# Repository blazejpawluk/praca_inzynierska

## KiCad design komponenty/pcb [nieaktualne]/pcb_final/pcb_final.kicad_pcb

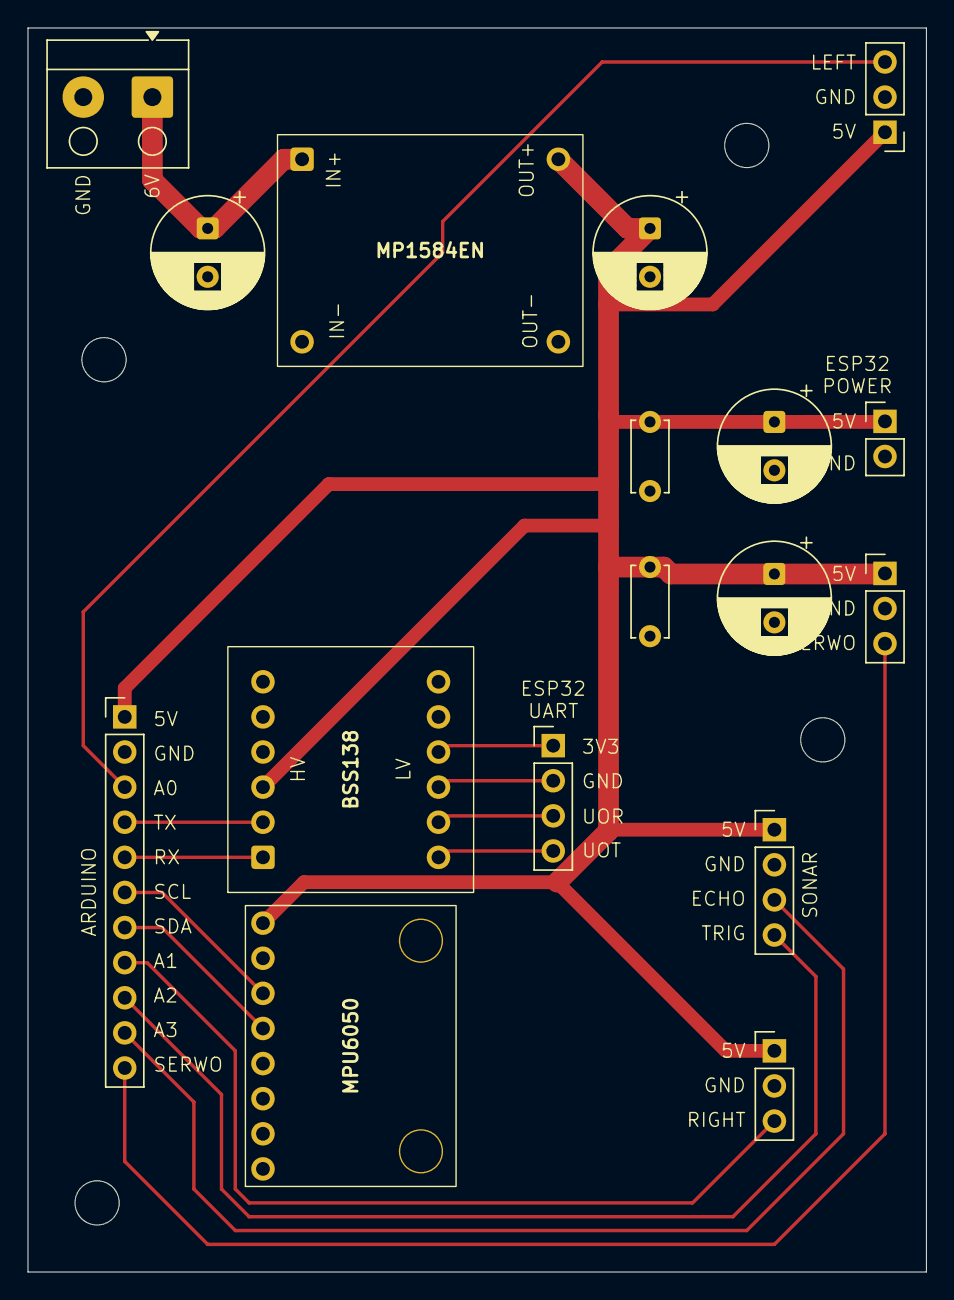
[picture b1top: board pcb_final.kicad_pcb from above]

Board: 2 copper layers, 65.0 x 90.0 mm, 17 parts (0 on the bottom side), 16 nets.

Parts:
C1, C2, C3, C5: 1000uF, 10V; CP_Radial_D8.0mm_P3.50mm
C4, C6: 100nF; C_Disc_D5.0mm_W2.5mm_P5.00mm
J1: LEFT_SENSOR; PinHeader_1x03_P2.54mm_Vertical
J2.1: ESP32_UART; PinHeader_1x04_P2.54mm_Vertical
J2.2: ESP32_POWER; PinHeader_1x02_P2.54mm_Vertical
J3: SERWO; PinHeader_1x03_P2.54mm_Vertical
J4: SONAR; PinHeader_1x04_P2.54mm_Vertical
J5: RIGHT_SENSOR; PinHeader_1x03_P2.54mm_Vertical
J6: ARDUINO; PinHeader_1x11_P2.54mm_Vertical
P1: POWER; Altech_AK100_1x02_P5.00mm
U1: MP1584EN
U2: BSS138; BSS138_2x6
U3: MPU6050

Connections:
/3V3: J2.1.2, U2.9 (LV)
/5V: C2.1, C3.1, C4.2, C5.1, C6.1, J1.1, J2.2.1, J3.1, J4.1, J5.1, J6.1, U1.3 (OUT+), U2.3 (HV), U3.8 (5V)
/+6V: C1.1, P1.1, U1.1 (IN+)
/A0: J1.3, J6.3
/A1: J5.3, J6.8
/A2: J4.4, J6.9
/A3: J4.3, J6.10
/GND: C1.2, C2.2, C3.2, C4.1, C5.2, C6.2, J1.2, J2.2.2, J3.2, J4.2, J5.2, J6.2, P1.2, U1.2 (IN-), U1.4 (OUT-), U2.4 (GND), U3.7 (GND)
/GND_ESP: J2.1.1, U2.10 (GND)
/RX: J6.5, U2.1 (HV1)
/SCL: J6.6, U3.6 (SCL)
/SDA: J6.7, U3.5 (SDA)
/SERWO: J3.3, J6.11
/TX: J6.4, U2.2 (HV2)
/UOR: J2.1.3, U2.8 (LV2)
/UOT: J2.1.4, U2.7 (LV1)

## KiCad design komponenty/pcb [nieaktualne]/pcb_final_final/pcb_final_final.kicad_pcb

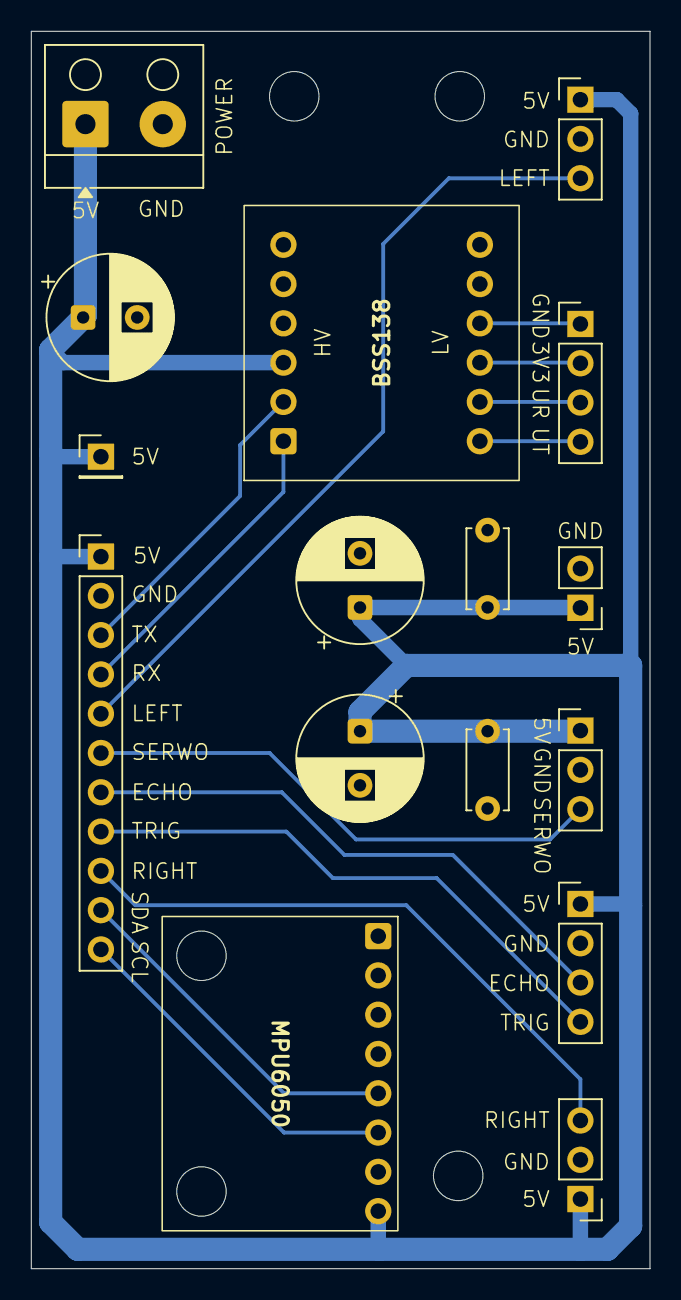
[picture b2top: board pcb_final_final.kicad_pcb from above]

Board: 2 copper layers, 40.0 x 80.0 mm, 16 parts (0 on the bottom side), 15 nets.

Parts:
C1, C2, C4: 1000uF 10V; CP_Radial_D8.0mm_P3.50mm
C3, C5: 100nF; C_Disc_D5.0mm_W2.5mm_P5.00mm
J1: POWER; Altech_AK100_1x02_P5.00mm
J2: SENSOR_LEFT; PinHeader_1x03_P2.54mm_Vertical
J3: ESP32-UART; PinHeader_1x04_P2.54mm_Vertical
J4: ESP32-POWER; PinHeader_1x02_P2.54mm_Vertical
J5: SERWO; PinHeader_1x03_P2.54mm_Vertical
J6: SONAR; PinHeader_1x04_P2.54mm_Vertical
J7: SENSOR_RIGHT; PinHeader_1x03_P2.54mm_Vertical
J8: ARDUINO; PinHeader_1x11_P2.54mm_Vertical
J9: L298N; PinHeader_1x01_P2.54mm_Vertical
U1: BSS138; BSS138_2x6
U2: MPU6050

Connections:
/3V3: J3.2, U1.9 (LV)
/5V: C1.1, C2.1, C3.1, C4.1, C5.1, J1.1, J2.1, J4.1, J5.1, J6.1, J7.1, J8.1, J9.1 (Pin_1_1), U1.3 (HV), U2.8 (5V)
/ECHO: J6.3, J8.7
/GND: C1.2, C2.2, C3.2, C4.2, C5.2, J1.2, J2.2, J4.2, J5.2, J6.2, J7.2, J8.2, U1.4 (GND), U2.7 (GND)
/GND_ESP: J3.1, U1.10 (GND)
/LEFT: J2.3, J8.5
/RIGHT: J7.3, J8.9
/RX: J8.4, U1.1 (HV1)
/SCL: J8.11, U2.6 (SCL)
/SDA: J8.10, U2.5 (SDA)
/SERWO: J5.3, J8.6
/TRIG: J6.4, J8.8
/TX: J8.3, U1.2 (HV2)
/UOR: J3.3, U1.8 (LV2)
/UOT: J3.4, U1.7 (LV1)
